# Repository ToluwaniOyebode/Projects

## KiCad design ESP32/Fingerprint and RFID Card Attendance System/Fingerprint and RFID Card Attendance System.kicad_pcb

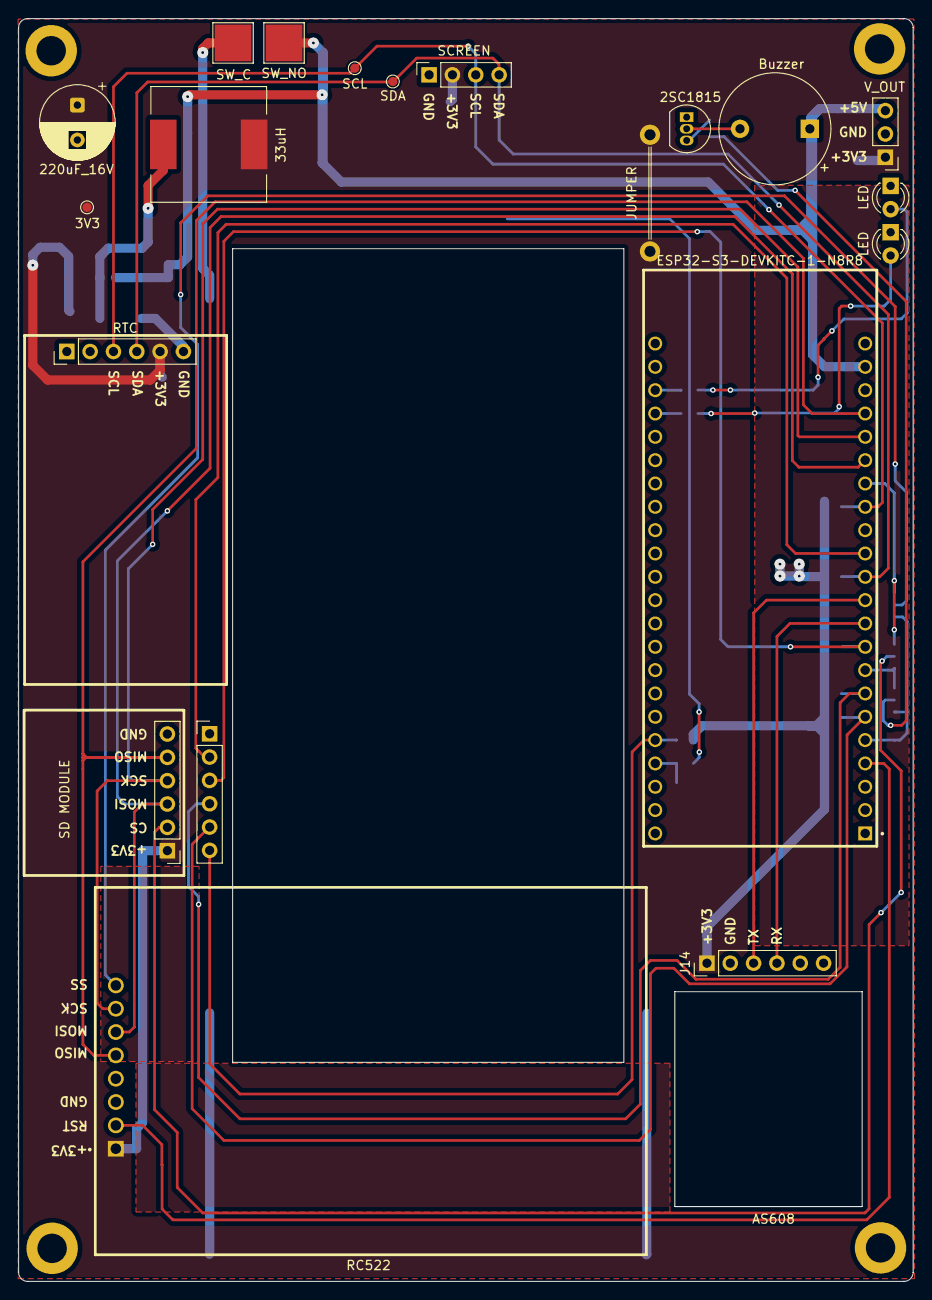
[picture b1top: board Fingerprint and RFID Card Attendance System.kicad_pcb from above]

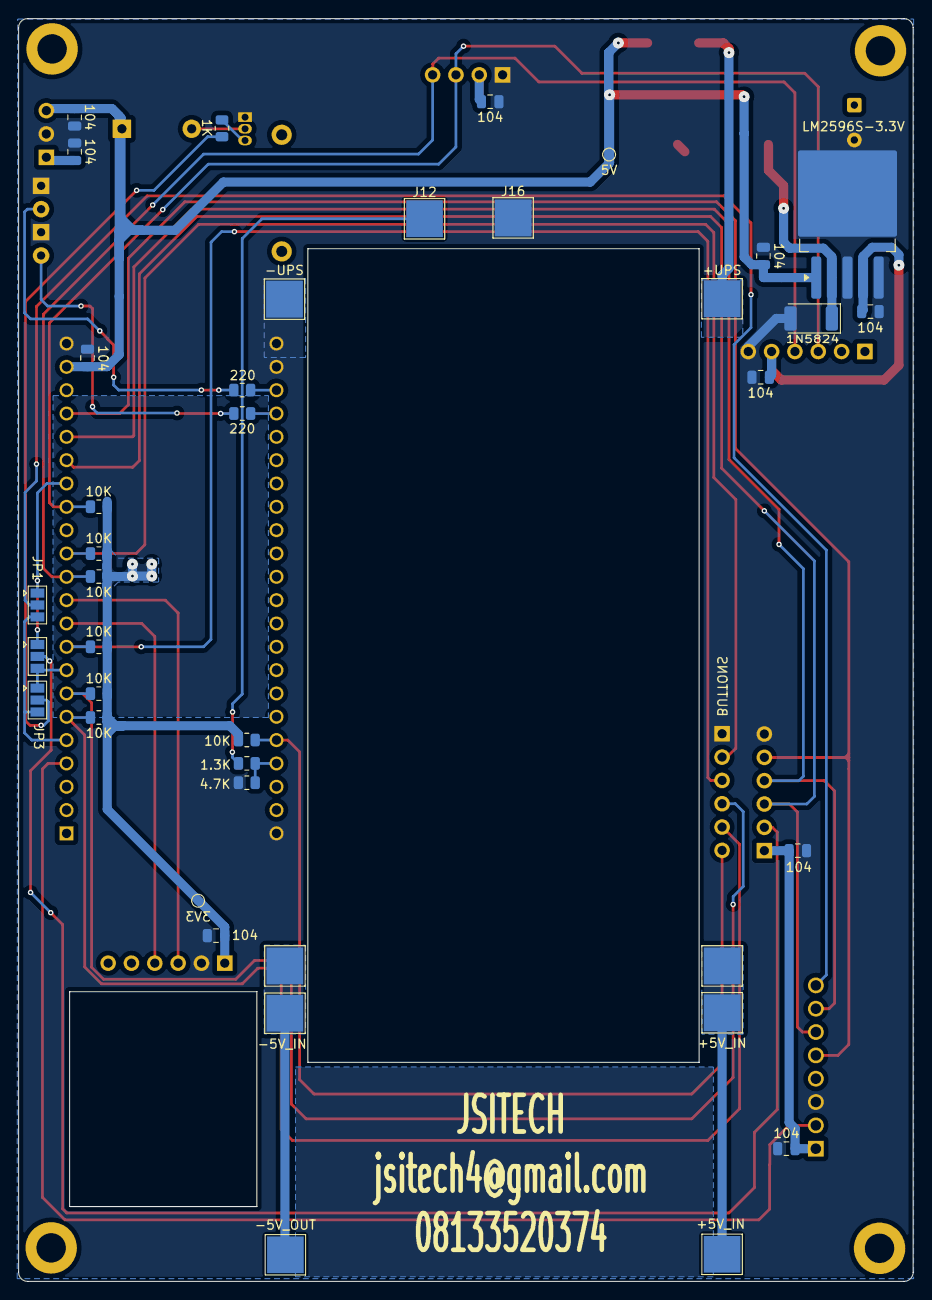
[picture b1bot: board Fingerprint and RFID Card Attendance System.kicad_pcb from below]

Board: 2 copper layers, 97.4 x 137.5 mm, 58 parts (39 on the bottom side), 34 nets.

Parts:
3.3V2, 3.3V5: 3V3; TestPoint_Pad_D1.0mm
5V1: 5V; TestPoint_Pad_D1.0mm
BZ1: Buzzer; Buzzer_12x9.5RM7.6
C1, C2, C3, C4, C5, C7, C8, C9, C10, C11: 104; C_0805_2012Metric
C6: 220uF_16V; CP_Radial_D8.0mm_P3.80mm
D1, D3: LED; LED_D3.0mm
D2: 1N5824; D_2010_5025Metric
GND: -UPS; TestPoint_Pad_4.0x4.0mm
IN+: +5V_IN; TestPoint_Pad_4.0x4.0mm
IN-: -5V_IN; TestPoint_Pad_4.0x4.0mm
J1: RTC; PinHeader_1x06_P2.54mm_Vertical
J2: SCREEN; PinSocket_1x04_P2.54mm_Vertical
J3, J5: +5V_IN; TestPoint_Pad_4.0x4.0mm
J4: -5V_OUT; TestPoint_Pad_4.0x4.0mm
J6: -5V_IN; TestPoint_Pad_4.0x4.0mm
J9: +UPS; TestPoint_Pad_4.0x4.0mm
J11: V_OUT; PinHeader_1x03_P2.54mm_Vertical
J12: +BATT; TestPoint_Pad_4.0x4.0mm
J13: BUTTONS; PinHeader_1x06_P2.54mm_Vertical
J14: AS608; PinHeader_1x06_P2.54mm_Vertical
J15: SD MODULE; PinHeader_1x06_P2.54mm_Vertical
J16: -BATT; TestPoint_Pad_4.0x4.0mm
J17: SW_C; TestPoint_Pad_4.0x4.0mm
J18: SW_NO; TestPoint_Pad_4.0x4.0mm
JP1, JP2, JP3: SolderJumper-3_P1.3mm_Open_Pad1.0x1.5mm
L1: 33uH; L_12x12mm_H4.5mm
Q1: 2SC1815; TO-92_Inline
R1, R2, R7, R8, R9, R10, R11: 10K; R_0805_2012Metric
R3, R4: 220; R_0805_2012Metric
R5: 1.3K; R_0805_2012Metric
R6: 4.7K; R_0805_2012Metric
R12: 1K; R_0805_2012Metric
SCL1: SCL; TestPoint_Pad_D1.0mm
SDA1: SDA; TestPoint_Pad_D1.0mm
U1: ESP32-S3-DEVKITC-1-N8R8; ESP32-S3-DEVKITC
U2: LM2596S-3.3V; TO-263-5_TabPin3
U3: RC522; RC522 RFID

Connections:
+3.3V: 3.3V2.1, 3.3V5.1, C1.1, C2.1, C5.1, C6.1, C8.1, C9.1, C10.1, C11.1, J1.5, J2.2, J11.1, J14.1, J15.1, L1.2, R1.1, R2.1, R7.1, R8.1, R9.1, R10.1, R11.1, U2.4 (FB), U3.1 (VCC)
+5V: 5V1.1, BZ1.1 (+), C3.1, C4.1, C7.1, J11.3, J18.1, U1.J1_21 (5V0), U2.1 (VIN)
/BTN1: J13.6, R11.2, U1.J3_5 (GPIO2)
/BTN2: J13.5, R10.2, U1.J1_6 (GPIO6)
/BTN3: J13.4, R9.2, U1.J1_7 (GPIO7)
/BTN4: J13.3, R8.2, U1.J1_9 (GPIO16)
/BTN5: J13.2, R7.2, U1.J1_13 (GPIO3)
/CS1: JP1.1 (A), JP2.1 (A), U1.J1_16 (GPIO10)
/CS2: JP2.3 (C), JP3.1 (A), U1.J1_8 (GPIO15)
/CS3: JP1.3 (C), JP3.3 (C), U1.J1_5 (GPIO5)
/RC522 RST: U1.J1_4 (GPIO4), U3.2 (RST)
/RC522 SS: JP1.2 (B), U3.8 (SS/SDA/RX)
/RX: J14.3, U1.J1_11 (GPIO18)
/SCL: J1.3, J2.3, R2.2, SCL1.1, U1.J1_15 (GPIO9)
/SD CARD CS: J15.2, JP2.2 (B)
/SDA: J1.4, J2.4, R1.2, SDA1.1, U1.J1_12 (GPIO8)
/SHARED_MISO: J15.5, U1.J1_19 (GPIO13), U3.5 (MISO/SCL/TX)
/SHARED_MOSI: J15.3, U1.J1_17 (GPIO11), U3.6 (MOSI)
/SHARED_SCK: J15.4, U1.J1_18 (GPIO12), U3.7 (SCK)
/TX: J14.4, U1.J1_10 (GPIO17)
GND: C1.2, C2.2, C3.2, C4.2, C5.2, C6.2, C7.2, C8.2, C9.2, C10.2, C11.2, D1.1 (K), D2.2 (A), D3.1 (K), GND.1, J1.6, J2.1, J11.2, J13.1, J14.2, J15.6, J16.1, Q1.1 (E), R6.2, U1.J1_22 (GND3), U1.J3_1 (GND), U1.J3_21 (GND1), U1.J3_22 (GND2), U2.3 (GND), U2.5 (~ON/OFF), U3.3 (GND)
unnamed: BZ1.2 (-), Q1.2 (C)
unnamed: D1.2 (A), R3.1
unnamed: D2.1 (K), L1.1, U2.2 (OUT)
unnamed: D3.2 (A), R4.1
unnamed: IN+.1, J3.1, J5.1
unnamed: IN-.1, J4.1, J6.1
unnamed: J12.1, R5.1
unnamed: J9.1, J17.1
unnamed: JP3.2 (B), R12.1
unnamed: Q1.3 (B), R12.2
unnamed: R5.2, R6.1, U1.J3_4 (GPIO1)
unnamed: R4.2, U1.J3_19 (USB_D+/GPIO20)
unnamed: R3.2, U1.J3_20 (USB_D-/GPIO19)

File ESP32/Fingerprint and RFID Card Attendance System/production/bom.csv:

Designator,Footprint,Quantity,Value,LCSC Part #
"3.3V2, 3.3V5",TestPoint_Pad_D1.0mm,2,3V3,
5V1,TestPoint_Pad_D1.0mm,1,5V,
BZ1,Buzzer_12x9.5RM7.6,1,Buzzer,
"C1, C10, C11, C2, C3, C4, C5, C7, C8, C9",0805,10,104,
C6,CP_Radial_D8.0mm_P3.80mm,1,220uF_16V,
"D1, D3",LED_D3.0mm,2,LED,
D2,2010,1,1N5824,
GND,TestPoint_Pad_4.0x4.0mm,1,-UPS,
"IN+, J3, J5",TestPoint_Pad_4.0x4.0mm,3,+5V_IN,
"IN-, J6",TestPoint_Pad_4.0x4.0mm,2,-5V_IN,
J1,PinHeader_1x06_P2.54mm_Vertical,1,RTC,
J11,PinHeader_1x03_P2.54mm_Vertical,1,V_OUT,
J12,TestPoint_Pad_4.0x4.0mm,1,+BATT,
J13,PinHeader_1x06_P2.54mm_Vertical,1,BUTTONS,
J14,PinHeader_1x06_P2.54mm_Vertical,1,AS608,
J15,PinHeader_1x06_P2.54mm_Vertical,1,SD MODULE,
J16,TestPoint_Pad_4.0x4.0mm,1,-BATT,
J17,TestPoint_Pad_4.0x4.0mm,1,SW_C,
J18,TestPoint_Pad_4.0x4.0mm,1,SW_NO,
J2,PinSocket_1x04_P2.54mm_Vertical,1,SCREEN,
J4,TestPoint_Pad_4.0x4.0mm,1,-5V_OUT,
J9,TestPoint_Pad_4.0x4.0mm,1,+UPS,
"JP1, JP2, JP3",SolderJumper-3_P1.3mm_Open_Pad1.0x1.5mm,3,~,
L1,L_12x12mm_H4.5mm,1,33uH,
Q1,TO-92_Inline,1,2SC1815,
"R1, R10, R11, R2, R7, R8, R9",0805,7,10K,
R12,0805,1,1K,
"R3, R4",0805,2,220,
R5,0805,1,1.3K,
R6,0805,1,4.7K,
SCL1,TestPoint_Pad_D1.0mm,1,SCL,
SDA1,TestPoint_Pad_D1.0mm,1,SDA,
U1,ESP32-S3-DEVKITC,1,ESP32-S3-DEVKITC-1-N8R8,
U2,TO-263-5_TabPin3,1,LM2596S-3.3V,
U3,RC522 RFID,1,RC522,

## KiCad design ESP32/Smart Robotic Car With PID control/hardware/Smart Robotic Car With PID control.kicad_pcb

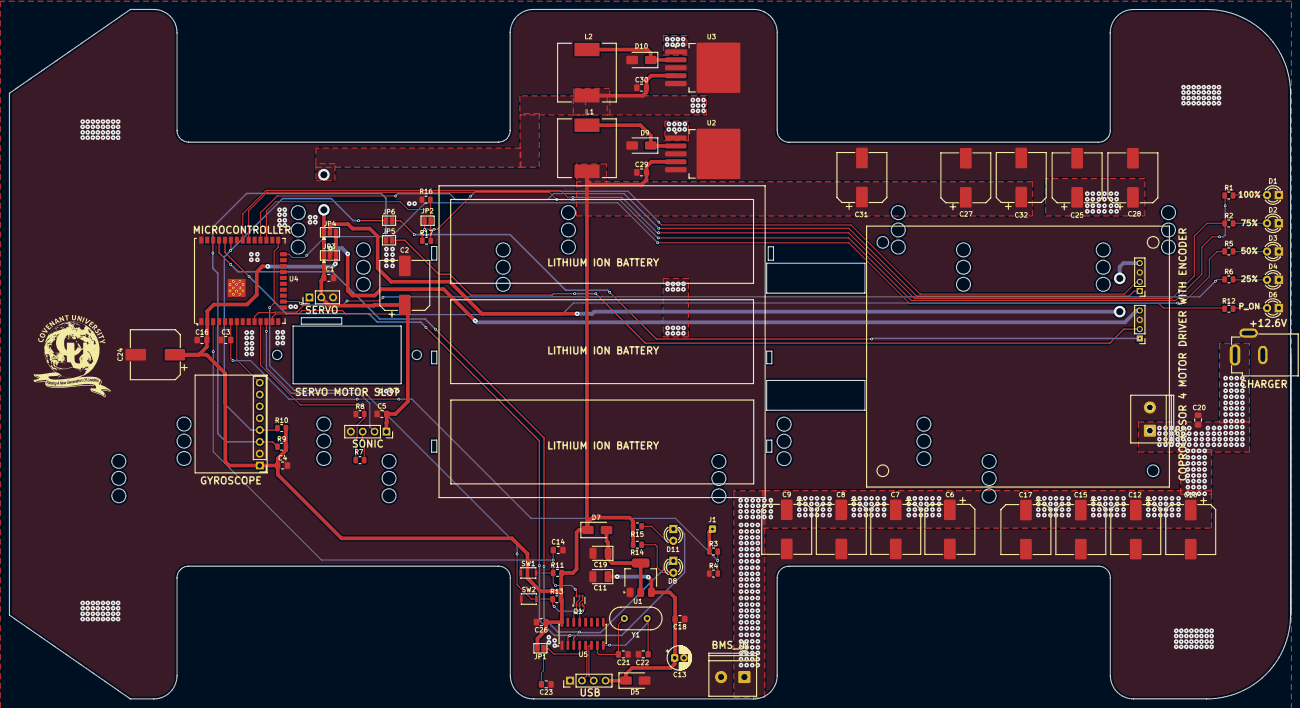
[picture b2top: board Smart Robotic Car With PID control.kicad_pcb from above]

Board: 2 copper layers, 275.0 x 148.0 mm, 87 parts (0 on the bottom side), 47 nets.

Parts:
C1, C3, C4, C5, C16, C18, C20, C23, C26, C29, C30: 100nF; C_0805_2012Metric_Pad1.18x1.45mm_HandSolder
C2, C6, C7, C8, C9, C10, C12, C15, C17: 680uF_35V; CP_Elec_10x12.5
C11, C19: 4.7uF/16V; CP_EIA-3528-21_Kemet-B_HandSolder
C13: 10uF_16V; CP_Radial_D5.0mm_P2.00mm
C14: 470nF; C_0805_2012Metric_Pad1.18x1.45mm_HandSolder
C21, C22: 22pF; C_0805_2012Metric_Pad1.18x1.45mm_HandSolder
C24, C25, C31: 470uF_16V; CP_Elec_10x12.5
C27, C28, C32: 220uF_16V; CP_Elec_10x12.5
D1, D2, D3, D4, D6, D8: Red; LED_D3.0mm
D5, D7: 1N5819; D_SMA
D9, D10: 1N5824; D_SMA
D11: Green; LED_D3.0mm
J1: BSENS; SolderWire-0.1sqmm_1x01_D0.4mm_OD1mm
J9: Ultra Sonic; PinSocket_1x04_P2.54mm_Vertical
J14: MPU6050; PinHeader_1x08_P2.54mm_Vertical
J15: UART; PinHeader_1x04_P2.00mm_Vertical
J16: I2C; PinHeader_1x04_P2.00mm_Vertical
J17: 12V IN; TerminalBlock_Phoenix_PT-1,5-2-5.0-H_1x02_P5.00mm_Horizontal
J18: USB_C Conn; PinHeader_1x04_P2.54mm_Vertical
J19: BMS; TerminalBlock_Phoenix_PT-1,5-2-5.0-H_1x02_P5.00mm_Horizontal
J20: CHARGER; Barrel_Jack_PTH_Slot
JP1, JP2, JP5, JP6: SolderJumper-2_P1.3mm_Open_Pad1.0x1.5mm
JP3, JP4: SolderJumper_3_Open; SolderJumper-3_P1.3mm_Open_Pad1.0x1.5mm
L1, L2: 33uH; L_12x12mm_H6mm
M1: Motor_Servo; PinHeader_1x03_P2.54mm_Vertical
Q1: UMH3N; SOT-363_SC-70-6
R1, R2, R5, R6, R12, R14, R15: 330R; R_0805_2012Metric
R3: 68k; R_0805_2012Metric
R4: 18k; R_0805_2012Metric
R7: 1k; R_0805_2012Metric
R8: 2k; R_0805_2012Metric
R9, R10, R11, R13, R16: 10k; R_0805_2012Metric
R17: 20k; R_0805_2012Metric
SW1: RESET; SW_SPST_CK_KXT3
SW2: FLASH; SW_SPST_CK_KXT3
U1: AMS1117-3.3; SOT-223-3_TabPin2
U2: LM2596S-3.3V; TO-263-5_TabPin6
U3: LM2596S-5V; TO-263-5_TabPin6
U4: ESP32-WROOM; ESP32-WROOM-32U
U5: CH340C; SOIC-16_3.9x9.9mm_P1.27mm
Y1: 12MHz; Crystal_HC49-4H_Vertical

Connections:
+3.3V: C4.2, C16.2, C24.1, C26.1, C27.1, C29.2, C31.1, C32.1, D7.1 (K), J14.1, JP1.2 (B), JP3.3 (B), JP4.3 (B), L1.2, R9.1, R10.2, R11.2, R13.2, R14.1, R15.1, U2.4 (FB), U4.2 (VDD), U5.16 (VCC)
+5V: C1.2, C2.1, C5.2, C25.1, C28.1, C30.2, J9.1, JP3.1 (A), JP4.1 (A), L2.2, M1.2 (+), U3.4 (FB)
+BATT: J1.1, R3.1
/+: J18.2, U5.5 (UD+)
/-: J18.3, U5.6 (UD-)
/A: J15.4, JP4.2 (C)
/B: J16.4, JP3.2 (C)
/DTR: Q1.2 (B1), Q1.4 (E2), U5.13 (~DTR)
/EN: C14.2, Q1.6 (C1), R11.1, SW1.2, U4.3 (EN)
/GPIO0: Q1.3 (C2), R13.1, SW2.2, U4.25 (IOA0)
/GPIO1/TX: D8.1 (K), U4.35 (TXD0/IO1), U5.3 (RXD)
/GPIO2: R12.1, U4.24 (IOA2)
/GPIO3/RX: D11.1 (K), U4.34 (RXD0/IO3), U5.2 (TXD)
/GPIO13: R6.1, U4.16 (IOA13)
/GPIO14: R5.1, U4.13 (IOA14)
/GPIO16: JP2.1 (A), R16.1, R17.2, U4.27 (IO16)
/GPIO17: J15.1, U4.28 (IO17)
/GPIO18: R1.1, U4.30 (IO18)
/GPIO19: R2.1, U4.31 (IO19)
/GPIO25: M1.1 (PWM), U4.10 (IOA25)
/GPIO26: R7.2, R8.2, U4.11 (IOA26)
/GPIO27: J9.2, U4.12 (IOA27)
/GPIO34: C3.2, R3.2, R4.2, U4.6 (IA34)
/GPIO35: J14.8, U4.7 (IA35)
/RTS: Q1.1 (E1), Q1.5 (B2), U5.14 (~RTS)
/SCL: J14.3, JP5.2 (B), R9.2, U4.36 (IO22)
/SDA: J14.4, JP6.2 (B), R10.1, U4.33 (IO21)
GND: C1.1, C2.2, C3.1, C4.1, C5.1, C6.2, C7.2, C8.2, C9.2, C10.2, C11.2, C12.2, C13.2, C14.1, C15.2, C16.1, C17.2, C18.1, C19.2, C20.1, C21.2, C22.2, C23.1, C24.2, C25.2, C26.2, C27.2, C28.2, C29.1, C30.1, C31.2, C32.2, D1.1 (K), D2.1 (K), D3.1 (K), D4.1 (K), D5.2 (A), D6.1 (K), D9.2 (A), D10.2 (A), J9.4, J14.2, J15.3, J16.3, J17.2, J18.1, J19.2, J20.2, M1.3 (-), R4.1, R8.1, R16.2, SW1.1, SW2.1, U1.1 (GND), U2.3 (GND), U2.5 (~ON/OFF), U2.6 (GND), U3.3 (GND), U3.5 (~ON/OFF), U3.6 (GND), U4.1 (GND), U4.15 (GND), U4.38 (GND), U4.39 (GND), U5.1 (GND)
unnamed: D1.2 (A), R1.2
unnamed: D2.2 (A), R2.2
unnamed: D3.2 (A), R5.2
unnamed: D4.2 (A), R6.2
unnamed: C11.1, C13.1, C18.2, D5.1 (K), J18.4, U1.3 (VI)
unnamed: D6.2 (A), R12.2
unnamed: C19.1, D7.2 (A), U1.2 (VO)
unnamed: D8.2 (A), R14.2
unnamed: D9.1 (K), L1.1, U2.2 (OUT)
unnamed: D10.1 (K), L2.1, U3.2 (OUT)
unnamed: D11.2 (A), R15.2
unnamed: J9.3, R7.1
unnamed: J15.2, JP2.2 (B), R17.1
unnamed: J16.1, JP6.1 (A)
unnamed: J16.2, JP5.1 (A)
unnamed: C23.2, JP1.1 (A), U5.4 (V3)
unnamed: C21.1, U5.7 (Xi), Y1.2
unnamed: C22.1, U5.8 (Xo), Y1.1
VCC: C6.1, C7.1, C8.1, C9.1, C10.1, C12.1, C15.1, C17.1, C20.2, J17.1, J19.1, J20.1, U2.1 (VIN), U3.1 (VIN)
